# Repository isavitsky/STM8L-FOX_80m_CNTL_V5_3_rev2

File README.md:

# STM8L-FOX_80m_CNTL_V5_3_rev2
STM8L 80m fox controller schematics and PCB version 5.3 revision 2

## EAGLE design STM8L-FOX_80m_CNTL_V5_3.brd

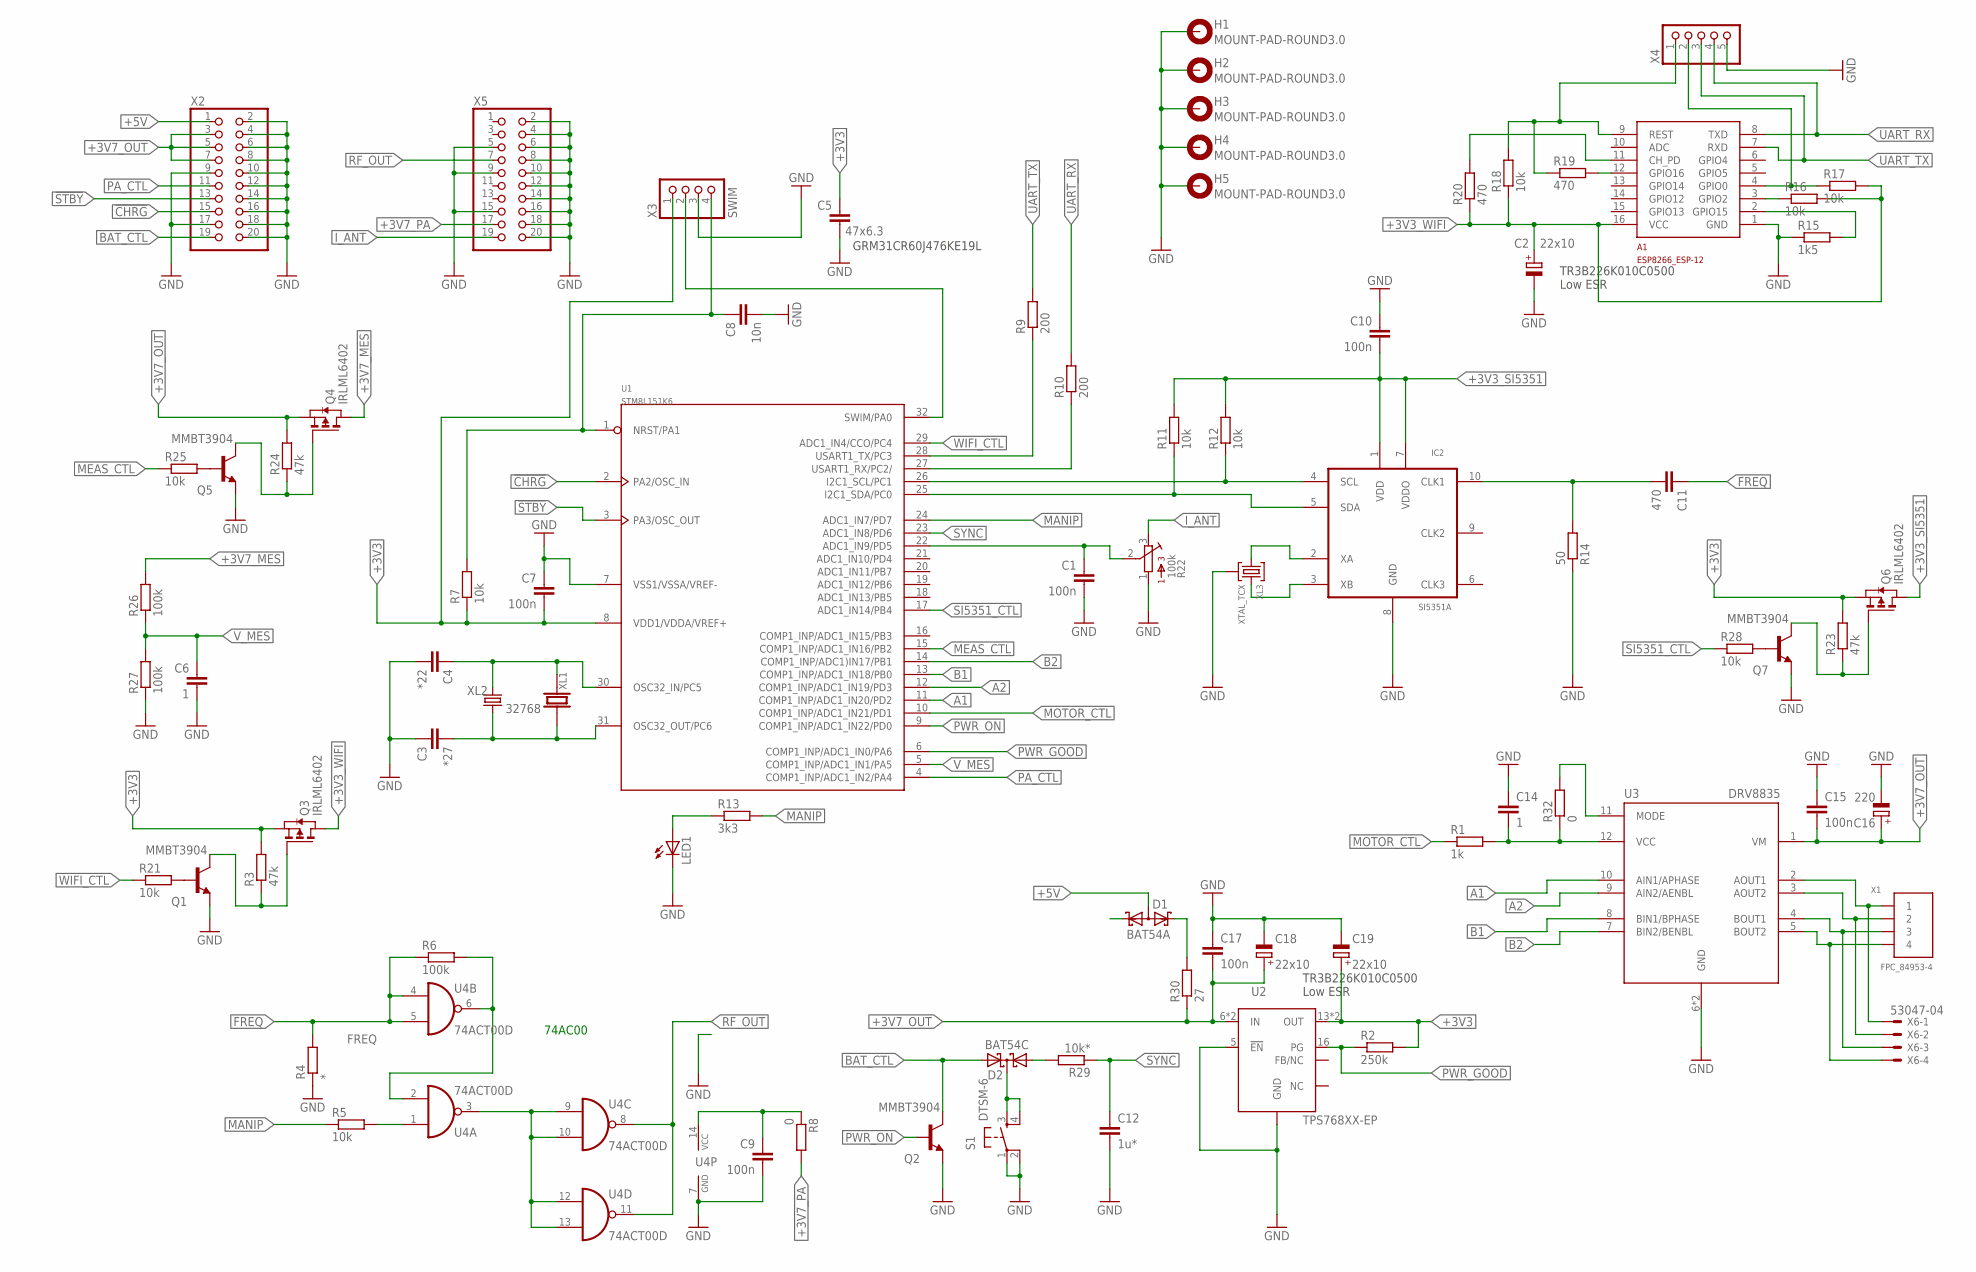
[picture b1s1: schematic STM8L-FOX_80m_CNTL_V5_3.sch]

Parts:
A1: ESP8266_ESP-12; ESP8266-ESP12
C1, C7, C9, C10, C15, C17: 100n; C1206K
C2, C18, C19: 22x10; B/3528-21W
C3: *27; C0805K
C4: *22; C0805K
C5: 47x6.3; C1206K
C6, C14: 1; C1206K
C8: 10n; C0805K
C11: 470; C1206K
C12: 1u*; C1206K
C16: 220; C/6032-28R
D1: BAT54A; SOT23
D2: BAT54C; SOT23
H1, H2, H3, H4, H5: MOUNT-PAD-ROUND3.0; 3,0-PAD
IC2: SI5351A; MSOP10
LED1: LED3MM
Q1, Q2, Q5, Q7: MMBT3904; SOT23-BEC
Q3, Q4, Q6: IRLML6402; SOT-23
R1: 1k; R1206
R2: 250k; R1206
R3, R23, R24: 47k; R1206
R4: *; R1206
R5, R7, R11, R12, R16, R17, R18, R21, R25, R28: 10k; R1206
R6, R26, R27: 100k; R1206
R8, R32: 0; R1206
R9, R10: 200; R1206
R13: 3k3; R1206
R14: 50; R1206
R15: 1k5; R1206
R19, R20: 470; R1206
R22: 100k; 3362R
R29: 10k*; R1206
R30: 27; R1206
S1: DTSM-6
U1: STM8L151K6; LQFP32-7X7
U2: TPS768XX-EP; TSSOP-20-PWP
U3: DRV8835; WSON_2X3
U4: 74ACT00D; SO14
X1: FPC_84953-4
X2, X5: PINHD-2X10; 2X10
X3: SWIM; 1X04
X4: PINHD-1X5; 1X05
X6: 53047-04
XL1: CRYSTALSMD; EPSON-MC146
XL2: 32768; TC38H-PCB
XL3: XTAL_TCX; TXC

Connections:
!CHRG!: U1.2 (PA2/OSC_IN), X2.15
!STBY!: U1.3 (PA3/OSC_OUT), X2.13
+3V3: C5.2, C7.1, C19.+, Q3.2 (S), Q6.2 (S), R2.2, R3.2, R7.1, R23.2, U1.8 (VDD1/VDDA/VREF+), U2.13 (OUT), U2.14 (OUT), X3.1
+3V3_SI5351: C10.1, IC2.1 (VDD), IC2.7 (VDDO), Q6.3 (D), R11.2, R12.2
+3V3_WIFI: A1.16 (VCC), C2.+, Q3.3 (D), R16.2, R17.2, R18.1, R20.1
+3V7_MES: Q4.3 (D), R26.2
+3V7_OUT: C15.2, C16.+, C17.2, C18.+, Q4.2 (S), R24.2, R30.1, U2.6 (IN), U2.7 (IN), U3.1 (VM), X2.3, X2.5, X2.7
+3V7_PA: R8.2, X5.17
+5V: D1.3 (AA), X2.1
A1: U1.11 (COMP1_INP/ADC1_IN20/PD2), U3.10 (AIN1/APHASE)
A2: U1.12 (COMP1_INP/ADC1_IN19/PD3), U3.9 (AIN2/AENBL)
B1: U1.13 (COMP1_INP/ADC1_IN18/PB0), U3.8 (BIN1/BPHASE)
B2: U1.14 (COMP1_INP/ADC1)IN17/PB1), U3.7 (BIN2/BENBL)
BAT_CTL: D2.2 (A2), Q2.C, X2.19
FREQ: C11.1, R4.2, R6.1, U4.4 (I0), U4.5 (I1)
FRQ1: C11.2, IC2.10 (CLK1), R14.2
GND: A1.1 (GND), C1.1, C2.-, C3.1, C4.2, C5.1, C6.2, C7.2, C8.2, C9.2, C10.2, C12.2, C14.1, C15.1, C16.-, C17.1, C18.-, C19.-, H1.B3,0, H2.B3,0, H3.B3,0, H4.B3,0, H5.B3,0, IC2.8 (GND), LED1.K (C), Q1.E, Q2.E, Q5.E, Q7.E, R4.1, R14.1, R15.1, R22.1, R27.1, S1.1, S1.2, U1.7 (VSS1/VSSA/VREF-), U2.1 (GND), U2.2 (GND), U2.3 (GND), U2.5 (!EN!), U2.9 (GND), U2.10 (GND), U2.11 (GND), U2.12 (GND), U2.19 (GND), U2.20 (GND), U2.PAD (GND), U3.6 (GND), U3.PAD (GND), U4.7 (GND), X2.2, X2.4, X2.6, X2.8, X2.9, X2.10, X2.12, X2.14, X2.16, X2.17, X2.18, X2.20, X3.3, X4.5, X5.2, X5.4, X5.5, X5.6, X5.8, X5.9, X5.10, X5.12, X5.14, X5.15, X5.16, X5.18, X5.20, XL3.2, XL3.4 (2)
GP0: A1.4 (GPIO0), R17.1, X4.2
I_ANT: R22.3, X5.19
MANIP: R5.1, R13.2, U1.24 (ADC1_IN7/PD7)
MEAS_CTL: R25.1, U1.15 (COMP1_INP/ADC1_IN16/PB2)
MOTOR_CTL: R1.1, U1.10 (COMP1_INP/ADC1_IN21/PD1)
MOTR_ON: C14.2, R1.2, R32.1, U3.12 (VCC)
unnamed: D2.3 (CC), S1.3, S1.4
unnamed: C1.2, R22.2, U1.22 (ADC1_IN9/PD5)
unnamed: Q5.B, R25.2
unnamed: A1.2 (GPIO15), R15.2
unnamed: Q4.1 (G), Q5.C, R24.1
unnamed: D1.2 (K2), R30.2
unnamed: IC2.3 (XB), XL3.3
unnamed: U4.3 (O), U4.9 (I0), U4.10 (I1), U4.12 (I0), U4.13 (I1)
unnamed: IC2.2 (XA), XL3.1
unnamed: R6.2, U4.2 (I1), U4.6 (O)
unnamed: Q7.B, R28.2
unnamed: C4.1, U1.30 (OSC32_IN/PC5), XL1.P$1 (1), XL2.P$2 (2)
unnamed: D2.1 (A1), R29.2
unnamed: A1.3 (GPIO2), R16.1
unnamed: Q6.1 (G), Q7.C, R23.1
unnamed: A1.12 (GPIO16), R19.2
unnamed: Q1.B, R21.2
unnamed: A1.11 (CH_PD), R20.2
unnamed: LED1.A, R13.1
unnamed: R32.2, U3.11 (MODE)
unnamed: C3.2, U1.31 (OSC32_OUT/PC6), XL1.P$2 (2), XL2.P$1 (1)
unnamed: R5.2, U4.1 (I0)
unnamed: U3.2 (AOUT1), X1.1, X6.1
unnamed: U3.3 (AOUT2), X1.2, X6.2
unnamed: U3.4 (BOUT1), X1.3, X6.3
unnamed: U3.5 (BOUT2), X1.4, X6.4
unnamed: C9.1, R8.1, U4.14 (VCC)
unnamed: Q1.C, Q3.1 (G), R3.1
NRST: C8.1, R7.2, U1.1 (NRST/PA1), X3.4
PA_CTL: U1.4 (COMP1_INP/ADC1_IN2/PA4), X2.11
PWR_GOOD: R2.1, U1.6 (COMP1_INP/ADC1_IN0/PA6), U2.16 (PG)
PWR_ON: Q2.B, U1.9 (COMP1_INP/ADC1_IN22/PD0)
RESET: A1.9 (REST), R18.2, R19.1, X4.1
RF_OUT: U4.8 (O), U4.11 (O), X5.7
SCL: IC2.4 (SCL), R12.1, U1.26 (I2C1_SCL/PC1)
SDA: IC2.5 (SDA), R11.1, U1.25 (I2C1_SDA/PC0)
SI5351_CTL: R28.1, U1.17 (ADC1_IN14/PB4)
SWIM: U1.32 (SWIM/PA0), X3.2
SYNC: C12.1, R29.1, U1.23 (ADC1_IN8/PD6)
UART_RX: A1.8 (TXD), R10.2, X4.4
UART_TX: A1.7 (RXD), R9.2, X4.3
USART1_RX: R10.1, U1.27 (USART1_RX/PC2/)
USART1_TX: R9.1, U1.28 (USART1_TX/PC3)
V_MES: C6.1, R26.1, R27.2, U1.5 (COMP1_INP/ADC1_IN1/PA5)
WIFI_CTL: R21.1, U1.29 (ADC1_IN4/CCO/PC4)

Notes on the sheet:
GRM31CR60J476KE19L
74AC00
TR3B226K010C0500 Low ESR

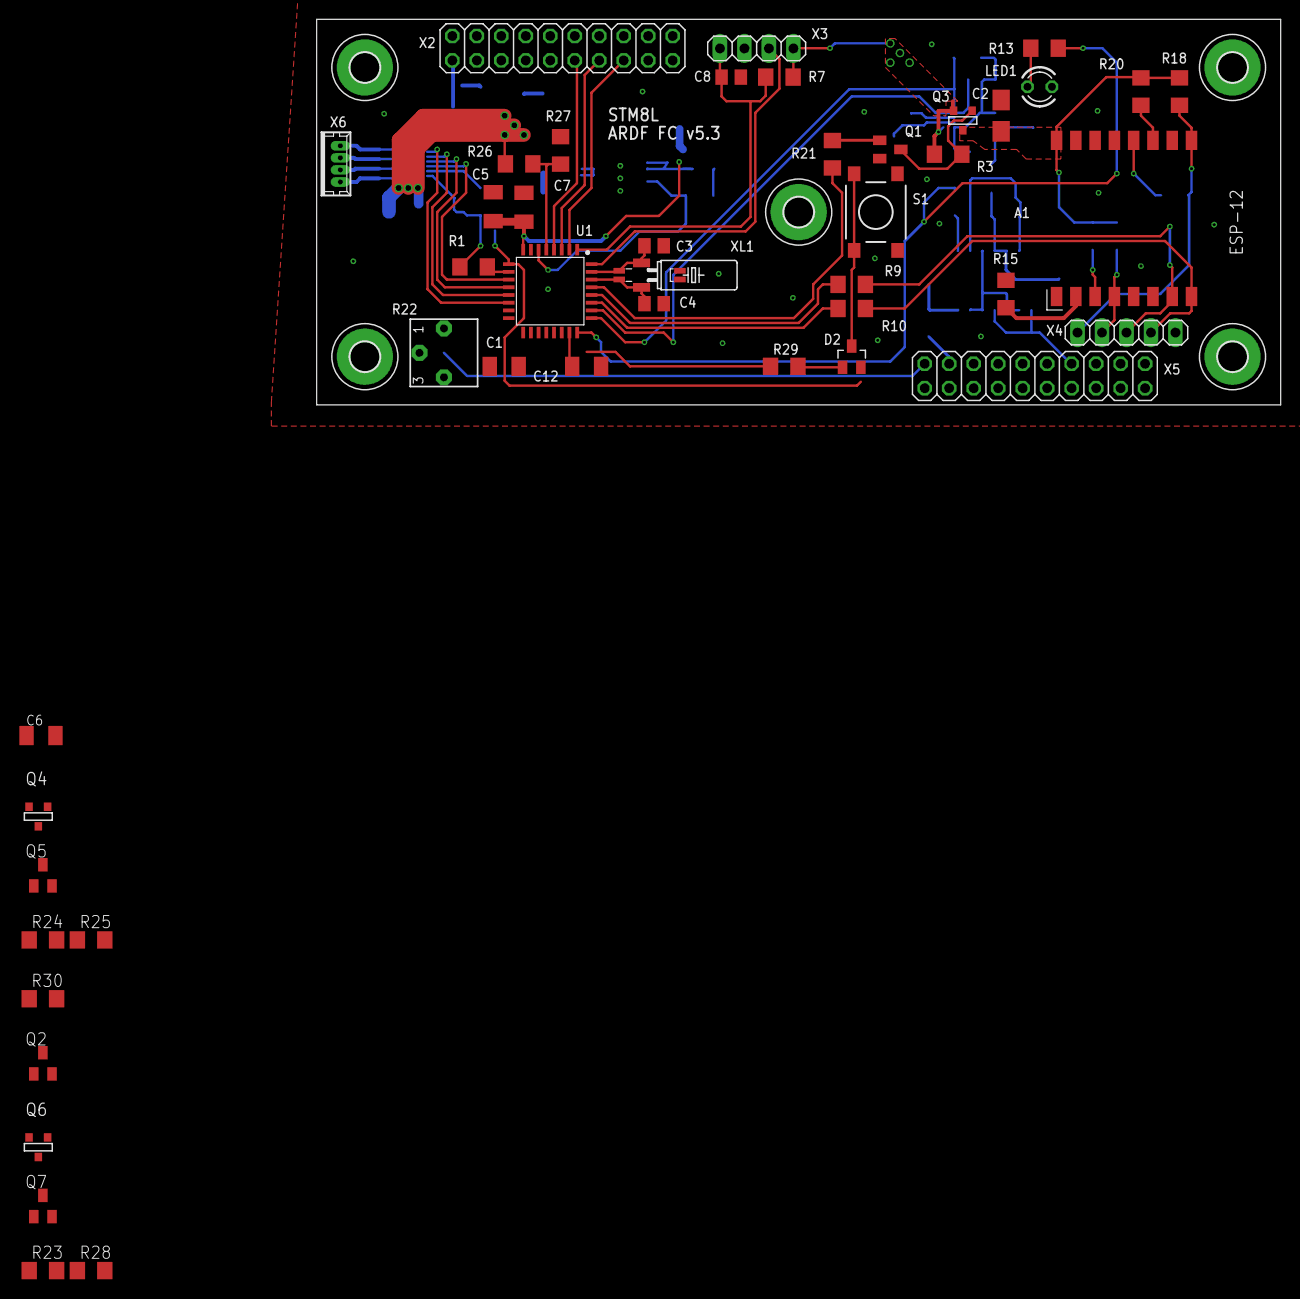
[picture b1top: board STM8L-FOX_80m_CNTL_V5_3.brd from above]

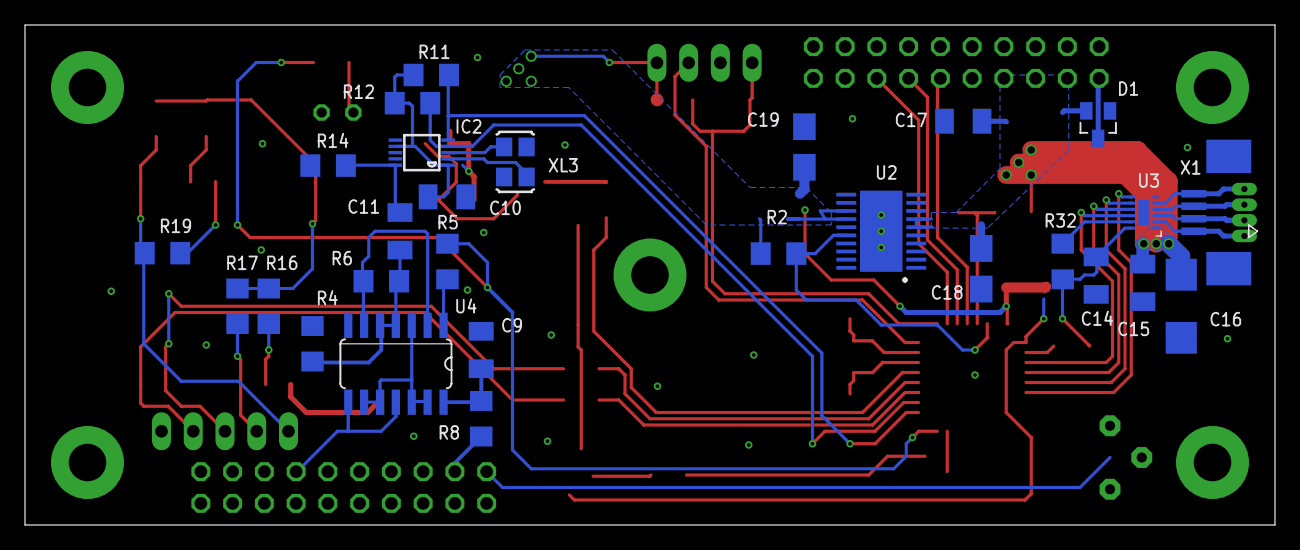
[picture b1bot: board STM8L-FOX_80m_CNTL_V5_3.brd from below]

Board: 2 copper layers, 100.0 x 40.0 mm, 80 parts (28 on the bottom side), 68 nets.
